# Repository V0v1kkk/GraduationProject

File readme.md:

# Разработка аппаратно-программного комплекса для оперативного мониторинга качества воздуха в жилых помещениях
Цель работы – разработать аппаратно-программный комплекс, с помощью которого можно оперативно получать данные о качестве воздуха, параметрах микроклимата, содержании монооксида углерода, двуокиси углерода, взвешенных частиц и природного газа в воздухе жилых помещений.

В процессе работы: 
* Изучена предметная область.
* Рассмотрены аналоги разработанного устройства, представленные на рынке. 
* Произведён выбор датчиков, наиболее подходящих для использования в устройстве, 
    а также рассмотрены вопросы, связанные с получением корректных данных от них. 
* Построена [диаграмма потоков данных](Images/DFD.png).
* Разработана [принципиальная схема устройства](Images/схема.png). 
* Разработаны прошивки для двух микроконтроллеров, 
    входящих в состав устройства (**[1](DataCollector/), [2](MainController/)**). 
* Разработан [графический интерфейс](Images/Интерфейс.png), представленный [ЖК-дисплеем](Nextion/) (**[1](Images/gui/1.png), [2](Images/gui/2.png), [3](Images/gui/3.png), [4](Images/gui/4.png), [5](Images/gui/5.png), [6](Images/gui/6.png), [7](Images/gui/7.png), [8](Images/gui/8.png), [9](Images/gui/9.png), [10](Images/10.png)**) и 
[web-интерфейс](WebInterface/) (**[1](Images/1.png), [2](Images/2.png), [3](Images/3.png), [4](Images/4.png), [5](Images/5.png)**). 
* Написано руководство пользователя. 
* Построен прототип устройства.

## [Пояснительная записка](Text/Диплом.pdf)

## Видео

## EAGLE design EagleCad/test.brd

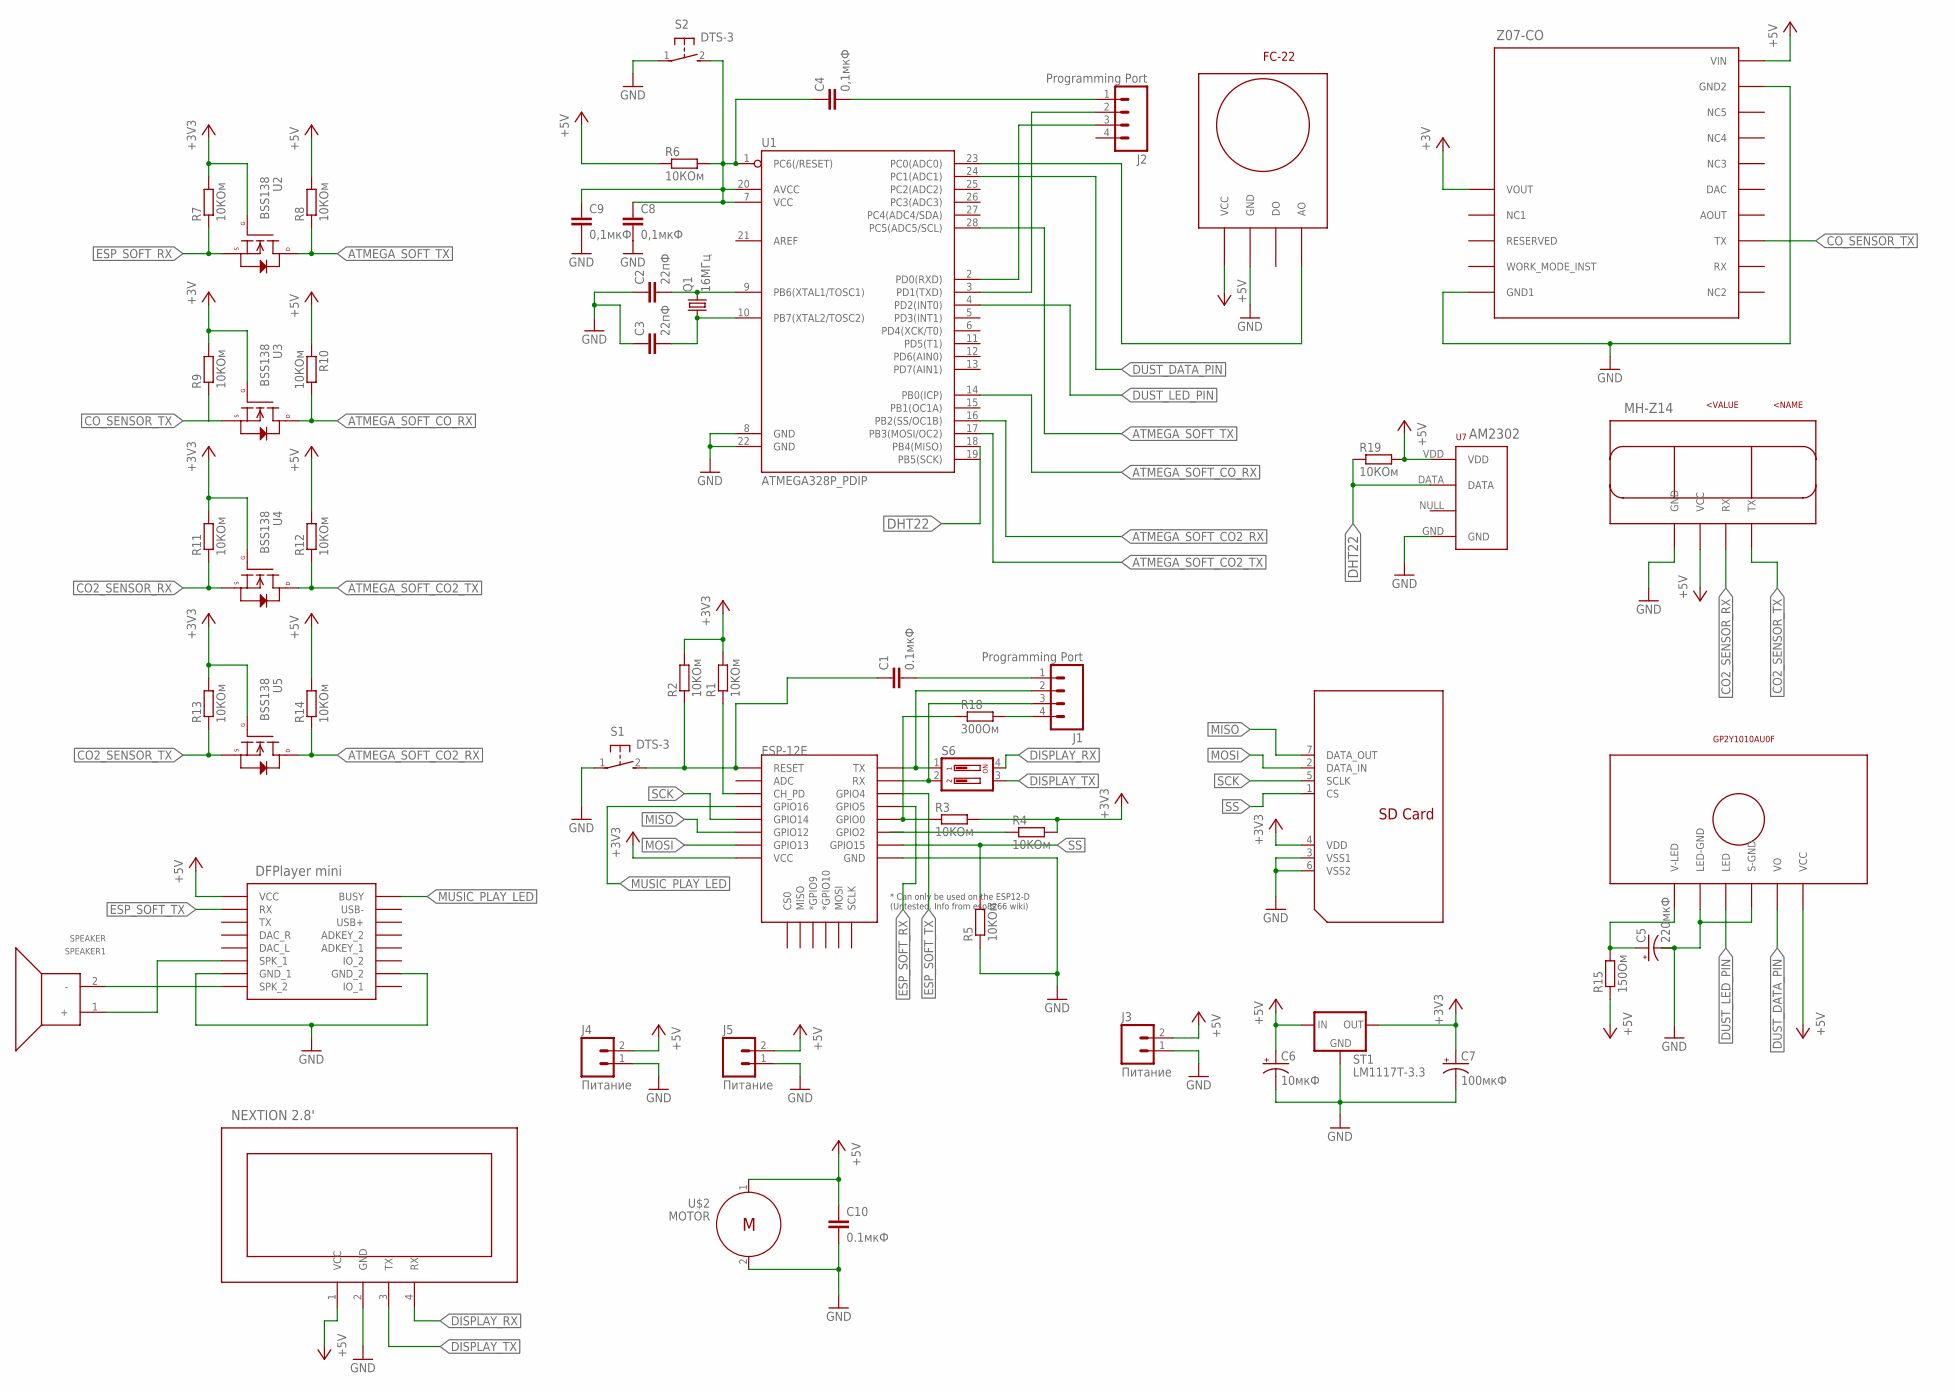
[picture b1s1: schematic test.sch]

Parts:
C1, C10: 0.1мкФ; CAP-PTH-SMALL-KIT
C2, C3: 22пФ; CAP-PTH-SMALL-KIT
C4, C8, C9: 0,1мкФ; CAP-PTH-SMALL-KIT
C5: 220мкФ; CPOL-RADIAL-10UF-25V-KIT
C6: 10мкФ; CPOL-RADIAL-10UF-25V-KIT
C7: 100мкФ; CPOL-RADIAL-10UF-25V-KIT
ESP-12E: ESP12ESMD; ESP12E-SMD
FC-22: FC-22FC-22-STANDART; FC-22
GP2Y1010AU0F: GP2Y1010AU0FGP2Y1010AU0F; 1X06
J1, J2: Programming Port; 1X04
J3, J4, J5: Питание; 1X02
MH-Z14: MH-Z14; 1X04
NEXTION1: NEXTION; 1X04
Q1: 16МГц; HC49/S
R1, R2, R3, R4, R5: 10KОм; 0207/10
R6, R7, R8, R9, R10, R11, R12, R13, R14, R19: 10КОм; 0207/10
R15: 150Ом; 0207/10
R18: 300Ом; 0207/10
S1, S2: DTS-3
S6: DS02; DS-02
SDCARD-1: SDCARDSDSTAY; SD
SPEAKER1: SPEAKER; 1X02
ST1: LM1117T-3.3; 78XXL
U1: ATMEGA328P_PDIP; DIL28-3
U2, U3, U4, U5: BSS138; SOT23-3
U7: RHT03_DHT-22_AM2302; RHT03_DHT-22
U$1: DFPLAYER
U$2: MOTOR; 1X02
Z07-CO-1: ZE07-CO; Z07-CO

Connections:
+3V3: C7.1 (+), ESP-12E.VCC, R1.2, R2.2, R3.2, R4.2, R7.2, R11.2, R13.2, ST1.GND (OUT), U2.1 (G), U4.1 (G), U5.1 (G)
+5V: C6.1 (+), C10.1, FC-22.1 (VCC), GP2Y1010AU0F.6 (VCC), J3.2, J4.2, J5.2, MH-Z14.3 (VCC), NEXTION1.1 (VCC), R6.1, R8.2, R10.1, R12.2, R14.2, R15.1, R19.2, ST1.OUT (IN), U7.VDD, U$1.VCC, U$2.1, Z07-CO-1.15 (VIN)
ATMEGA_SOFT_CO2_RX: R14.1, U1.16 (PB2(SS/OC1B)), U5.3 (D)
ATMEGA_SOFT_CO2_TX: R12.1, U1.17 (PB3(MOSI/OC2)), U4.3 (D)
ATMEGA_SOFT_CO_RX: R10.2, U1.14 (PB0(ICP)), U3.3 (D)
ATMEGA_SOFT_TX: R8.1, U1.28 (PC5(ADC5/SCL)), U2.3 (D)
CO2_SENSOR_RX: MH-Z14.2 (RX), R11.1, U4.2 (S)
CO2_SENSOR_TX: MH-Z14.1 (TX), R13.1, U5.2 (S)
CO_SENSOR_TX: R9.1, U3.2 (S), Z07-CO-1.8 (TX)
DHT22: R19.1, U1.18 (PB4(MISO)), U7.DATA
DISPLAY_RX: NEXTION1.4 (RX), S6.4
DISPLAY_TX: NEXTION1.3 (TX), S6.3
DUST_DATA_PIN: GP2Y1010AU0F.5 (VO), U1.24 (PC1(ADC1))
DUST_LED_PIN: GP2Y1010AU0F.3 (LED), U1.4 (PD2(INT0))
ESP_SOFT_RX: ESP-12E.GPIO5, R7.1, U2.2 (S)
ESP_SOFT_TX: ESP-12E.GPIO4, U$1.RX
GND: C2.1, C3.1, C5.2 (-), C6.2 (-), C7.2 (-), C8.2, C9.2, C10.2, ESP-12E.GND, FC-22.2 (GND), GP2Y1010AU0F.2 (LED-GND), GP2Y1010AU0F.4 (S-GND), J3.1, J4.1, J5.1, MH-Z14.4 (GND), NEXTION1.2 (GND), R5.1, S1.1, S2.1, ST1.IN (GND), U1.8 (GND), U1.22 (GND), U7.GND, U$1.GND_1, U$1.GND_2, U$2.2, Z07-CO-1.5 (GND1), Z07-CO-1.14 (GND2)
MISO: ESP-12E.GPIO12, SDCARD-1.7 (DATA_OUT)
MOSI: ESP-12E.GPIO13, SDCARD-1.2 (DATA_IN)
MUSIC_PLAY_LED: ESP-12E.GPIO16, U$1.BUSY
unnamed: C5.1 (+), GP2Y1010AU0F.1 (V-LED), R15.2
unnamed: C4.1, C8.1, C9.1, R6.2, S2.2, U1.1 (PC6(/RESET)), U1.7 (VCC), U1.20 (AVCC)
unnamed: ESP-12E.CH_PD, R1.1
unnamed: ESP-12E.GPIO0, R3.1, R18.1
unnamed: ESP-12E.GPIO2, R4.1
unnamed: ESP-12E.RXD0 (RX), J1.3, S6.2
unnamed: C1.1, ESP-12E.RESET, R2.1, S1.2
unnamed: C1.2, J1.1
unnamed: ESP-12E.TXD0 (TX), J1.2, S6.1
unnamed: C3.2, Q1.1, U1.10 (PB7(XTAL2/TOSC2))
unnamed: SPEAKER1.1 (+), U$1.SPK1 (SPK_1)
unnamed: SPEAKER1.2 (-), U$1.SPK2 (SPK_2)
unnamed: C2.2, Q1.2, U1.9 (PB6(XTAL1/TOSC1))
unnamed: C4.2, J2.1
unnamed: J2.2, U1.3 (PD1(TXD))
unnamed: J1.4, R18.2
unnamed: J2.3, U1.2 (PD0(RXD))
unnamed: FC-22.4 (AO), U1.23 (PC0(ADC0))
SCK: ESP-12E.GPIO14, SDCARD-1.5 (SCLK)
SS: ESP-12E.GPIO15, R5.2, SDCARD-1.1 (CS)
VCC: R9.2, U3.1 (G), Z07-CO-1.1 (VOUT)
VDD: SDCARD-1.4 (VDD)
VSS2: SDCARD-1.3 (VSS1), SDCARD-1.6 (VSS2)

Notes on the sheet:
NEXTION 2.8'
DFPlayer mini
MH-Z14
Z07-CO
AM2302

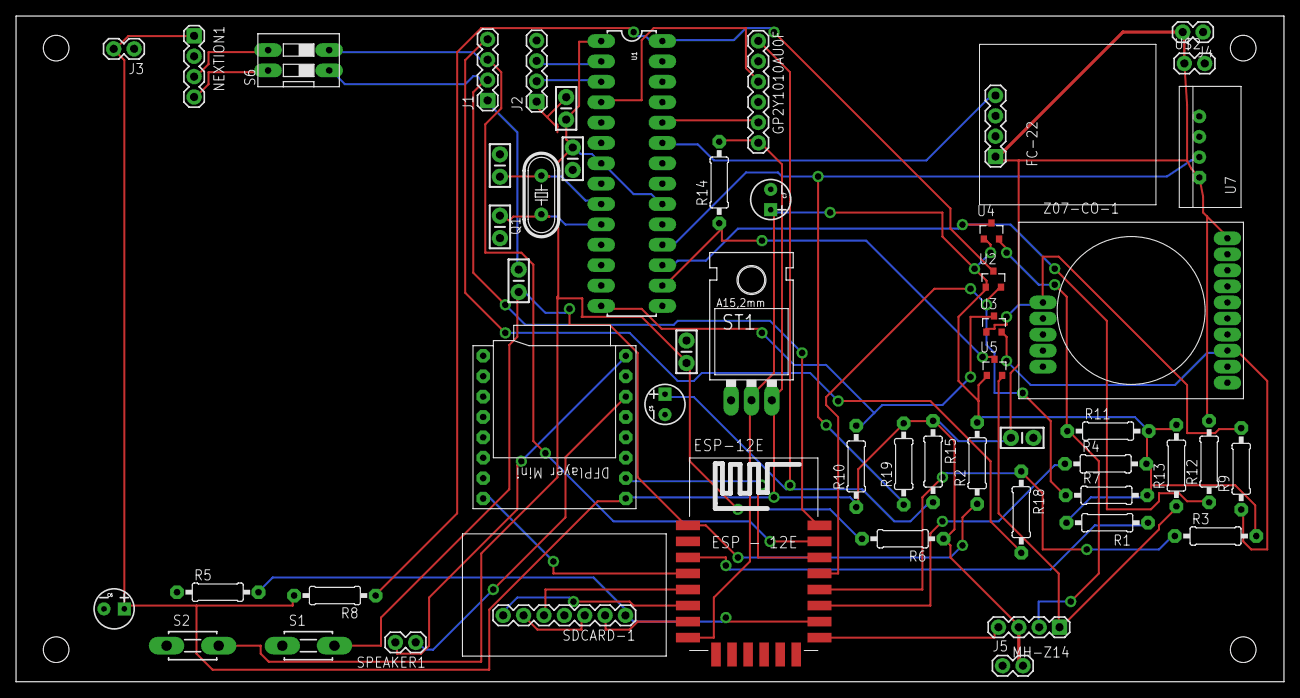
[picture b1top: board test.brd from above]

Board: 2 copper layers, 158.1 x 83.0 mm, 53 parts (0 on the bottom side), 42 nets.

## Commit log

2016-12-10 Initial commit.
2016-12-11 Video added to readme, removed "caps".
2016-12-11 Add spaces in readme.
2016-12-13 Small changes in readme

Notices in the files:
parts and their libraries:
SparkFun-Capacitors: Licensing: Creative Commons ShareAlike 4.0 International - https://creativecommons.org/licenses/by-sa/4.0
